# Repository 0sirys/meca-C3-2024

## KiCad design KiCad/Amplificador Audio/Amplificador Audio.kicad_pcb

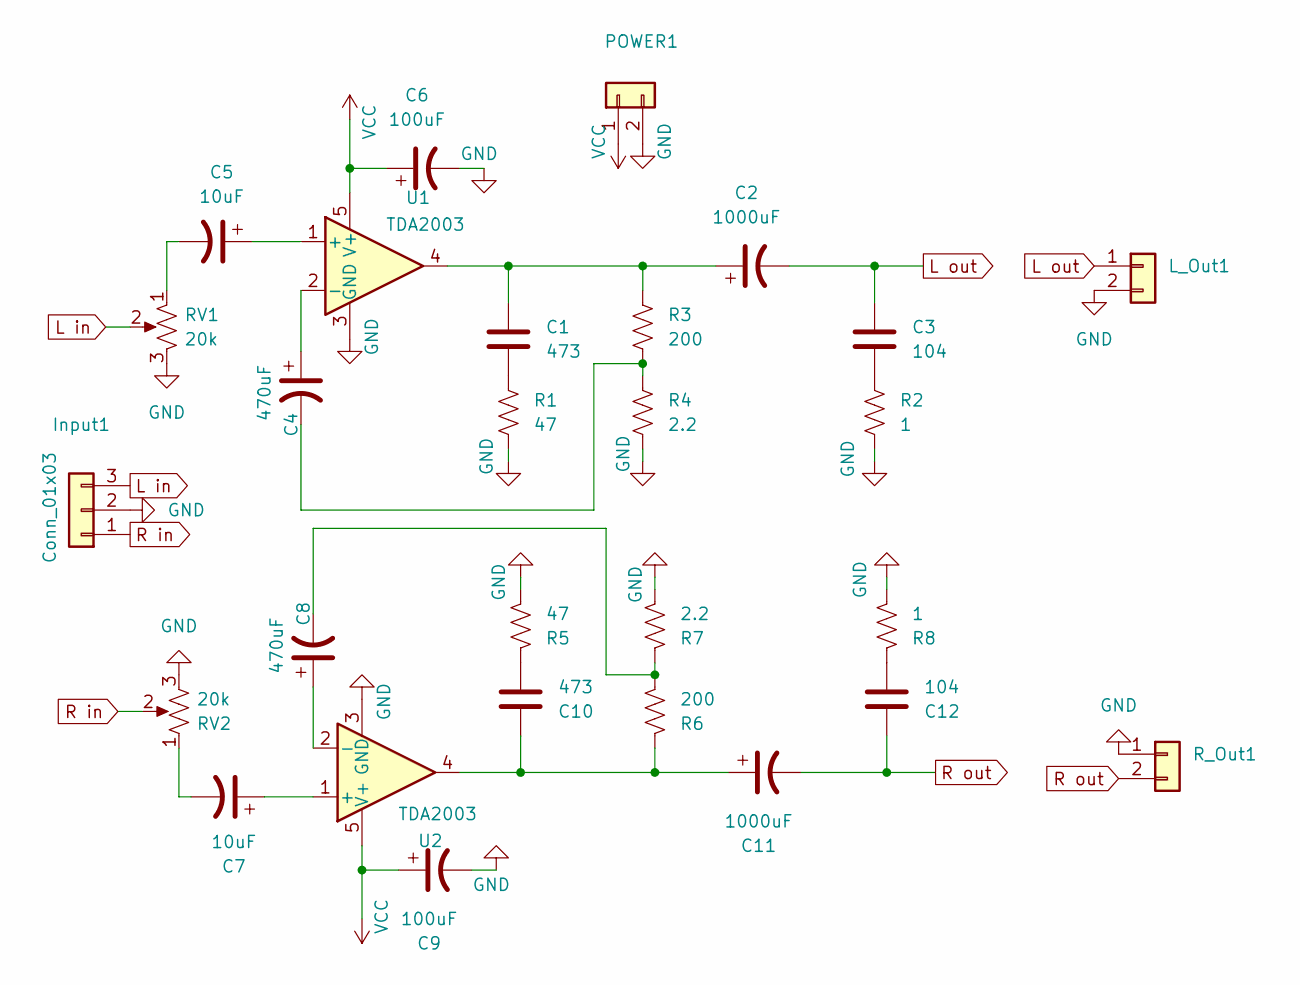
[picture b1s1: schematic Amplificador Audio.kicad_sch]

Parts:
C1, C10: 473; C_Disc_D3.0mm_W2.0mm_P2.50mm
C2, C11: 1000uF; CP_Radial_D16.0mm_P7.50mm
C3, C12: 104; C_Disc_D3.0mm_W2.0mm_P2.50mm
C4, C8: 470uF; CP_Radial_D10.0mm_P5.00mm
C5, C7: 10uF; CP_Radial_D5.0mm_P2.50mm
C6, C9: 100uF; CP_Radial_D10.0mm_P5.00mm
Input1: Conn_01x03; Molex_KK-254_AE-6410-03A_1x03_P2.54mm_Vertical
L_Out1: Conn_01x02; Molex_KK-254_AE-6410-02A_1x02_P2.54mm_Vertical
POWER1: CONN_01x02; Molex_KK-254_AE-6410-02A_1x02_P2.54mm_Vertical
R1, R5: 47; R_Axial_DIN0309_L9.0mm_D3.2mm_P15.24mm_Horizontal
R2, R8: 1; R_Axial_DIN0309_L9.0mm_D3.2mm_P15.24mm_Horizontal
R3, R6: 200; R_Axial_DIN0309_L9.0mm_D3.2mm_P15.24mm_Horizontal
R4, R7: 2.2; R_Axial_DIN0309_L9.0mm_D3.2mm_P15.24mm_Horizontal
RV1, RV2: 20k; Potentiometer_Runtron_RM-065_Vertical
R_Out1: Conn_01x02; Molex_KK-254_AE-6410-02A_1x02_P2.54mm_Vertical
U1, U2: TDA2003; TO-220-5_P3.4x3.7mm_StaggerOdd_Lead3.8mm_Vertical

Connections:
GND: C6.2, C9.2, Input1.2, L_Out1.2, POWER1.2, R1.2, R2.2, R4.2, R5.2, R7.2, R8.2, RV1.3, RV2.3, R_Out1.1, U1.3 (GND), U2.3 (GND)
L in: Input1.3, RV1.2
L out: C2.2, C3.1, L_Out1.1
unnamed: C1.1, C2.1, R3.1, U1.4
unnamed: C1.2, R1.1
unnamed: C3.2, R2.1
unnamed: C4.2, R3.2, R4.1
unnamed: C5.2, RV1.1
unnamed: C7.2, RV2.1
unnamed: C8.2, R6.2, R7.1
unnamed: C10.1, C11.1, R6.1, U2.4
unnamed: C10.2, R5.1
unnamed: C12.2, R8.1
unnamed: C5.1, U1.1 (+)
unnamed: C4.1, U1.2 (-)
unnamed: C7.1, U2.1 (+)
unnamed: C8.1, U2.2 (-)
R in: Input1.1, RV2.2
R out: C11.2, C12.1, R_Out1.2
VCC: C6.1, C9.1, POWER1.1, U1.5 (V+), U2.5 (V+)

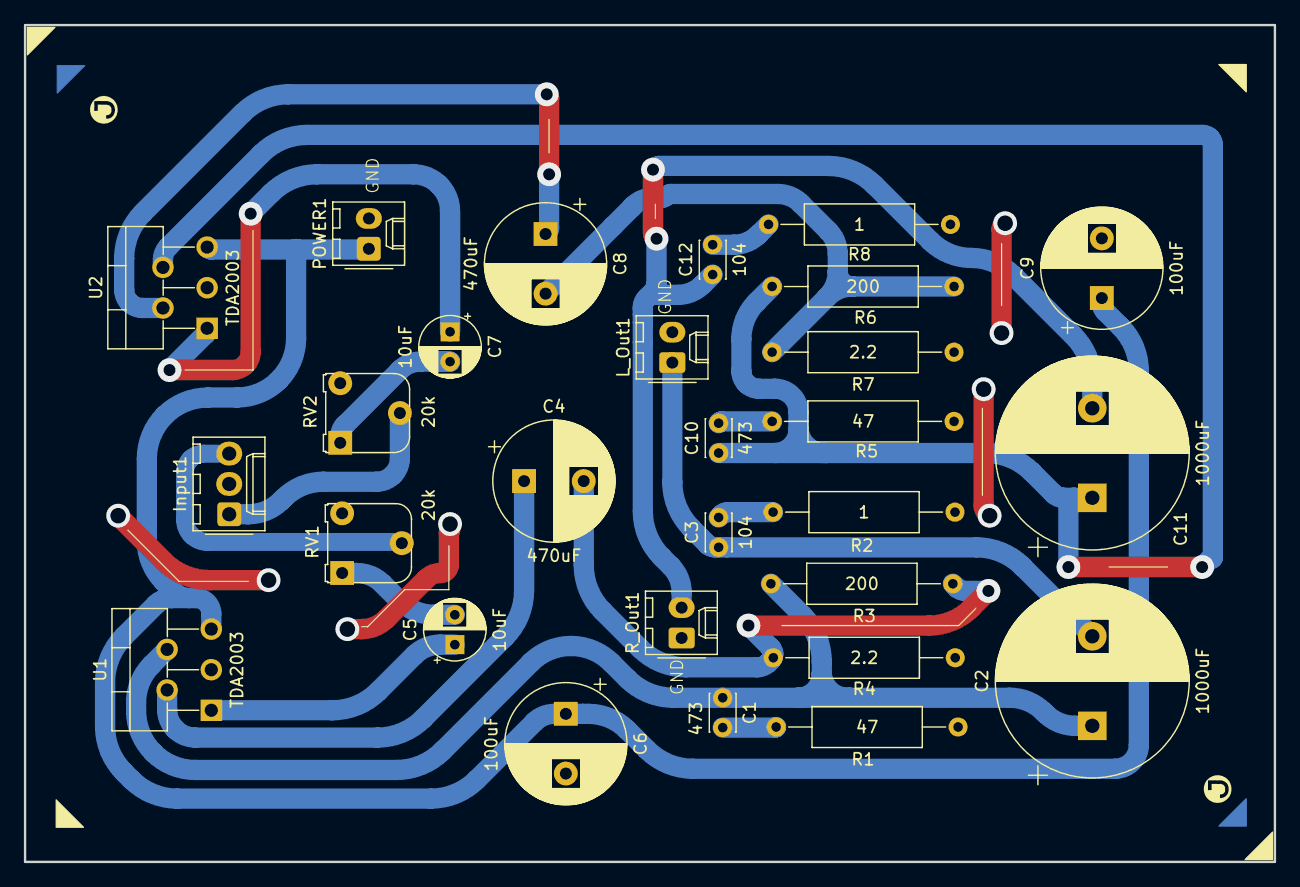
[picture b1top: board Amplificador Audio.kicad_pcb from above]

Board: 2 copper layers, 104.7 x 70.1 mm, 29 parts (0 on the bottom side), 20 nets.

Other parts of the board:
G2: LOGO; Logo

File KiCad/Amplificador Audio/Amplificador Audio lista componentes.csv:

Reference,Value,Qty
"C1,C10",473 mica,2
"C2,C11",1000uF,2
"C3,C12",104 mica,2
"C4,C8",470uF,2
"C5,C7",10uF,2
"C6,C9",100uF,2
Input1,Conn_01x03,1
"L_Out1,R_Out1",Conn_01x02,2
POWER1,Conn_01x02,1
"R1,R5",47,2
"R2,R8",1,2
"R3,R6",200,2
"R4,R7",2.2,2
"RV1,RV2",20k,2
"U1,U2",TDA2003,2

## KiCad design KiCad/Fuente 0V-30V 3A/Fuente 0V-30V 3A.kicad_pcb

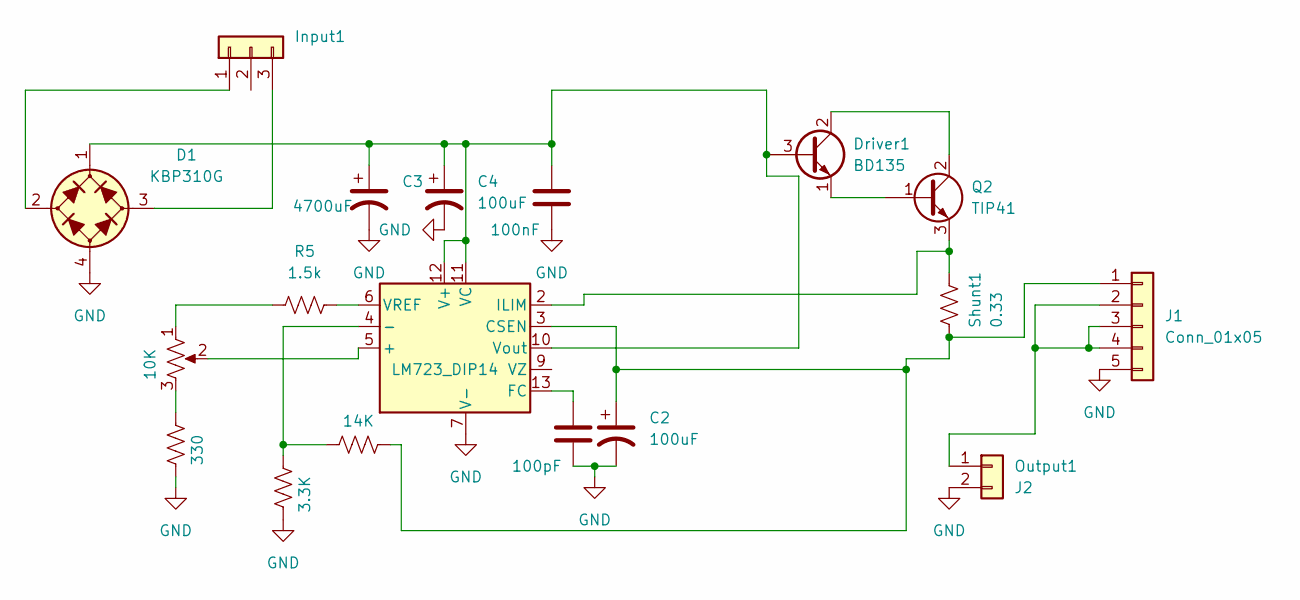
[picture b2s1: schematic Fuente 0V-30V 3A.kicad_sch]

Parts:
C1: 100pF; C_Disc_D5.0mm_W2.5mm_P2.50mm
C2, C4: 100uF; CP_Radial_Tantal_D8.0mm_P2.50mm
C3: 4700uF; C_Radial_D18.0mm_H35.5mm_P7.50mm
C5: 100nF; C_Disc_D5.0mm_W2.5mm_P2.50mm
D1: KBP310G; Diode_Bridge_KBP
Driver1: BD135; TO-126-3_Vertical
Input1: J3; Molex_KK-254_AE-6410-03A_1x03_P2.54mm_Vertical
J1: Conn_01x05; Molex_KK-254_AE-6410-05A_1x05_P2.54mm_Vertical
Output1: J2; Molex_KK-254_AE-6410-02A_1x02_P2.54mm_Vertical
Q2: TIP41; TO-220-3_Vertical
R1: 3.3K; R_Axial_DIN0411_L9.9mm_D3.6mm_P12.70mm_Horizontal
R4: 14K; R_Axial_DIN0411_L9.9mm_D3.6mm_P15.24mm_Horizontal
R5: 1.5k; R_Axial_DIN0411_L9.9mm_D3.6mm_P15.24mm_Horizontal
R6: 330; R_Axial_DIN0411_L9.9mm_D3.6mm_P15.24mm_Horizontal
RV1: 10K; Potentiometer_Alps_RK163_Single_Horizontal
Shunt1: 0.33; R_Axial_Power_L20.0mm_W6.4mm_P25.40mm
U1: LM723_DIP14; DIP-14_W7.62mm

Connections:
GND: C1.1, C2.2, C3.2, C4.2, C5.1, D1.4 (-), J1.5, Output1.2, R1.2, R6.1, U1.7 (V-)
unnamed: D1.2 (1), Input1.1
unnamed: D1.3 (2), Input1.3
unnamed: C3.1, C4.1, C5.2, D1.1 (+), Driver1.3 (B), U1.10 (Vout), U1.11 (VC), U1.12 (V+)
unnamed: Driver1.2 (C), Q2.2 (C)
unnamed: Driver1.1 (E), Q2.1 (B)
unnamed: C2.1, J1.1, R4.2, Shunt1.2, U1.3 (CSEN)
unnamed: J1.2, J1.3, J1.4, Output1.1
unnamed: Q2.3 (E), Shunt1.1, U1.2 (ILIM)
unnamed: R5.1, RV1.1
unnamed: R6.2, RV1.3
unnamed: RV1.2, U1.5 (+)
unnamed: R1.1, R4.1, U1.4 (-)
unnamed: C1.2, U1.13 (FC)
unnamed: R5.2, U1.6 (VREF)

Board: 2 copper layers, 18 parts (0 on the bottom side), 15 nets, no tracks yet.

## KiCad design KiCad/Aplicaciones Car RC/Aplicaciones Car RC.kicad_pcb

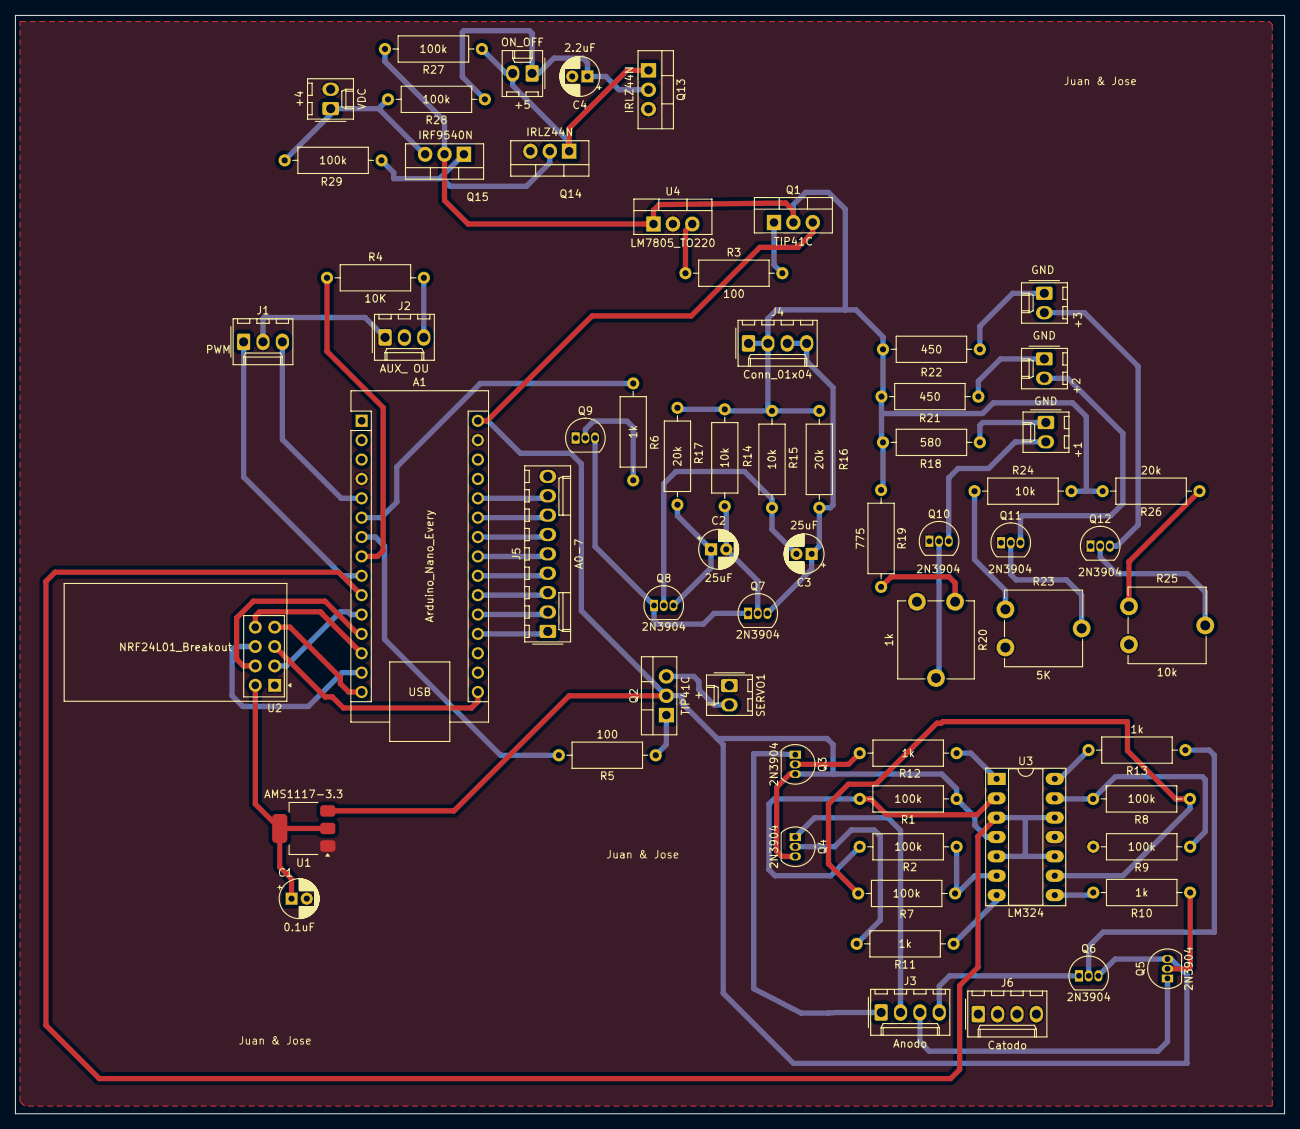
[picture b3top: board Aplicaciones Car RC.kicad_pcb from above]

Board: 2 copper layers, 166.4 x 144.0 mm, 65 parts (0 on the bottom side), 67 nets.

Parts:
+1, +2, +3: GND; Molex_KK-254_AE-6410-02A_1x02_P2.54mm_Vertical
+4: VDC; Molex_KK-254_AE-6410-02A_1x02_P2.54mm_Vertical
+5: ON_OFF; Molex_KK-254_AE-6410-02A_1x02_P2.54mm_Vertical
A1: Arduino_Nano_Every; Arduino_Nano
C1: 0.1uF; CP_Radial_D5.0mm_P2.00mm
C2, C3: 25uF; CP_Radial_D5.0mm_P2.00mm
C4: 2.2uF; CP_Radial_D5.0mm_P2.00mm
J1: PWM; Molex_KK-254_AE-6410-03A_1x03_P2.54mm_Vertical
J2: AUX_ OU; Molex_KK-254_AE-6410-03A_1x03_P2.54mm_Vertical
J3: Anodo; Molex_KK-254_AE-6410-04A_1x04_P2.54mm_Vertical
J4: Conn_01x04; Molex_KK-254_AE-6410-04A_1x04_P2.54mm_Vertical
J5: A0-7; Molex_KK-254_AE-6410-09A_1x09_P2.54mm_Vertical
J6: Catodo; Molex_KK-254_AE-6410-04A_1x04_P2.54mm_Vertical
Q1, Q2: TIP41C; TO-220-3_Vertical
Q3, Q4, Q5, Q6, Q7, Q8, Q9, Q10, Q11, Q12: 2N3904; TO-92_Inline
Q13, Q14: IRLZ44N; TO-220-3_Vertical
Q15: IRF9540N; TO-220-3_Vertical
R1, R2, R7, R8, R9, R27, R28, R29: 100k; R_Axial_DIN0309_L9.0mm_D3.2mm_P12.70mm_Horizontal
R3, R5: 100; R_Axial_DIN0309_L9.0mm_D3.2mm_P12.70mm_Horizontal
R4: 10K; R_Axial_DIN0309_L9.0mm_D3.2mm_P12.70mm_Horizontal
R6, R10, R11, R12, R13: 1k; R_Axial_DIN0309_L9.0mm_D3.2mm_P12.70mm_Horizontal
R14, R15, R24: 10k; R_Axial_DIN0309_L9.0mm_D3.2mm_P12.70mm_Horizontal
R16, R17, R26: 20k; R_Axial_DIN0309_L9.0mm_D3.2mm_P12.70mm_Horizontal
R18: 580; R_Axial_DIN0309_L9.0mm_D3.2mm_P12.70mm_Horizontal
R19: 775; R_Axial_DIN0309_L9.0mm_D3.2mm_P12.70mm_Horizontal
R20: 1k; Potentiometer_ACP_CA9-V10_Vertical
R21, R22: 450; R_Axial_DIN0309_L9.0mm_D3.2mm_P12.70mm_Horizontal
R23: 5K; Potentiometer_ACP_CA9-V10_Vertical
R25: 10k; Potentiometer_ACP_CA9-V10_Vertical
SERVO1: +; Molex_KK-254_AE-6410-02A_1x02_P2.54mm_Vertical
U1: AMS1117-3.3; SOT-223-3_TabPin2
U2: NRF24L01_Breakout; nRF24L01_Breakout
U3: LM324; DIP-14_W7.62mm_Socket_LongPads
U4: LM7805_TO220; TO-220-3_Vertical

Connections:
3.3: C1.1, U1.2 (VO), U2.2 (VCC)
+5V: A1.30 (VIN), Q1.3 (E), Q2.2 (C), Q3.3 (C), Q4.3 (C), Q5.3 (C), Q6.3 (C), R1.1, U1.3 (VI), U3.4 (V+)
+14V: J4.1, J4.2, Q1.2 (C), Q15.2 (D), R14.2, R15.2, R16.2, R17.2, R18.1, R19.1, R21.1, R22.1, R24.2, R26.2, R27.2, U4.1 (VI)
CE: A1.11 (D8), U2.3 (CE)
CSN: A1.12 (D9), U2.4 (~CSN)
GND: +4.2, A1.4 (GND), A1.29 (GND), C1.2, C4.2, J1.2, J2.1, J5.9, J6.1, J6.2, J6.3, J6.4, Q9.1 (E), Q10.1 (E), Q11.1 (E), Q12.1 (E), Q13.3 (S), Q14.3 (S), R9.2, R20.1 (a), R23.1 (a), R25.1 (a), SERVO1.1, U1.1 (GND), U2.1 (GND), U3.11 (V-), U4.2 (GND)
IRQ: A1.13 (D10), U2.8 (IRQ)
ITON: A1.8 (D5), R4.1
Luces: A1.6 (D3), R6.1
MISO: A1.15 (MISO), U2.7 (MISO)
MOSI: A1.14 (MOSI), U2.6 (MOSI)
unnamed: +1.1, R18.2
unnamed: +1.2, Q10.3 (C)
unnamed: +2.1, R21.2
unnamed: +2.2, Q11.3 (C)
unnamed: +3.1, R22.2
unnamed: +3.2, Q12.3 (C)
unnamed: +4.1, Q15.3 (S), R28.2, R29.2
unnamed: +5.1, C4.1, Q13.2 (D), R28.1
unnamed: +5.2, Q13.1 (G), Q14.1 (G), R27.1
unnamed: A1.19 (A0), J5.1
unnamed: A1.20 (A1), J5.2
unnamed: A1.21 (A2), J5.3
unnamed: A1.22 (A3), J5.4
unnamed: A1.25 (A6), J5.7
unnamed: A1.26 (A7), J5.8
unnamed: A1.24 (SCL/A5), J5.6
unnamed: A1.23 (SDA/A4), J5.5
unnamed: J2.3, R4.2
unnamed: J3.1, Q3.1 (E)
unnamed: J3.2, Q4.1 (E)
unnamed: J3.3, Q5.1 (E)
unnamed: J3.4, Q6.1 (E)
unnamed: C3.1, J4.3, J4.4, Q7.3 (C), R16.1
unnamed: Q1.1 (B), R3.2
unnamed: Q2.1 (B), R5.1
unnamed: Q2.3 (E), SERVO1.2
unnamed: Q3.2 (B), R12.1
unnamed: Q4.2 (B), R11.2
unnamed: Q5.2 (B), R10.1
unnamed: Q6.2 (B), R13.1
unnamed: C2.2, Q7.2 (B), R14.1
unnamed: Q7.1 (E), Q8.1 (E), Q9.3 (C)
unnamed: C3.2, Q8.2 (B), R15.1
unnamed: C2.1, Q8.3 (C), R17.1
unnamed: Q9.2 (B), R6.2
unnamed: Q10.2 (B), R20.2 (b)
unnamed: Q11.2 (B), R23.2 (b)
unnamed: Q12.2 (B), R25.2 (b)
unnamed: Q14.2 (D), Q15.1 (G), R29.1
unnamed: R10.2, U3.8
unnamed: R11.1, U3.7
unnamed: R12.2, U3.1
unnamed: R13.2, U3.14
unnamed: R19.2, R20.3 (c)
unnamed: R23.3 (c), R24.1
unnamed: R25.3 (c), R26.1
unnamed: R1.2, R2.1, U3.2 (-)
unnamed: R2.2, R7.1, U3.6 (-)
unnamed: R7.2, R8.1, U3.9 (-)
unnamed: R8.2, R9.1, U3.13 (-)
unnamed: R3.1, U4.3 (VO)
PWM D: A1.7 (D4), R5.2
PWM M: A1.5 (D2), J1.3
PWM M2: A1.9 (D6), J1.1
PWM S: A1.10 (D7), U3.3 (+), U3.5 (+), U3.10 (+), U3.12 (+)
SCK: A1.16 (SCK), U2.5 (SCK)

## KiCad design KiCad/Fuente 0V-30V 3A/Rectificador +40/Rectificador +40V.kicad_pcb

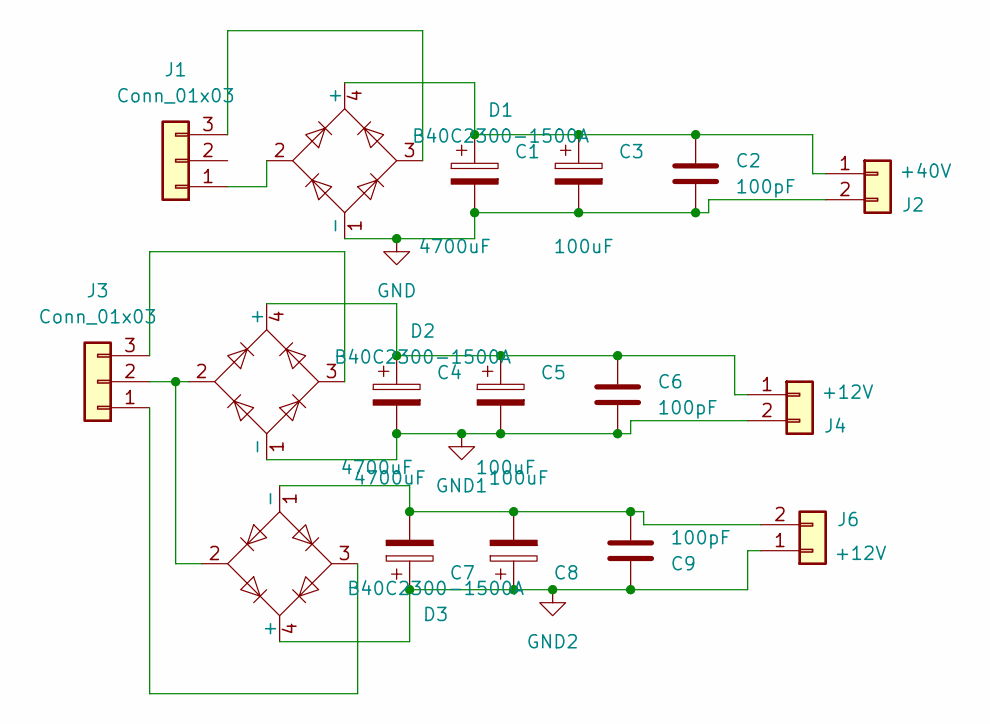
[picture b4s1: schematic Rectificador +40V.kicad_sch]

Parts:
C1, C4, C7: 4700uF; C_Radial_D18.0mm_H35.5mm_P7.50mm
C2, C6, C9: 100pF; C_Disc_D3.4mm_W2.1mm_P2.50mm
C3, C5, C8: 100uF; C_Radial_D10.0mm_H16.0mm_P5.00mm
D1, D2, D3: B40C2300-1500A; Diode_Bridge_19.0x3.5x10.0mm_P5.0mm
J1, J3: Conn_01x03; Molex_KK-254_AE-6410-03A_1x03_P2.54mm_Vertical
J2: +40V; Molex_KK-254_AE-6410-02A_1x02_P2.54mm_Vertical
J4, J6: +12V; Molex_KK-254_AE-6410-02A_1x02_P2.54mm_Vertical

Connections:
unnamed: C1.1, C2.1, C3.1, D1.4 (+), J2.1
unnamed: C1.2, C2.2, C3.2, D1.1 (-), J2.2
unnamed: C4.1, C5.1, C6.1, D2.4 (+), J4.1
unnamed: C4.2, C5.2, C6.2, D2.1 (-), J4.2
unnamed: C7.1, C8.1, C9.1, D3.4 (+), J6.1
unnamed: C7.2, C8.2, C9.2, D3.1 (-), J6.2
unnamed: D1.2, J1.1
unnamed: D1.3, J1.3
unnamed: D3.3, J3.1
unnamed: D2.2, D3.2, J3.2
unnamed: D2.3, J3.3

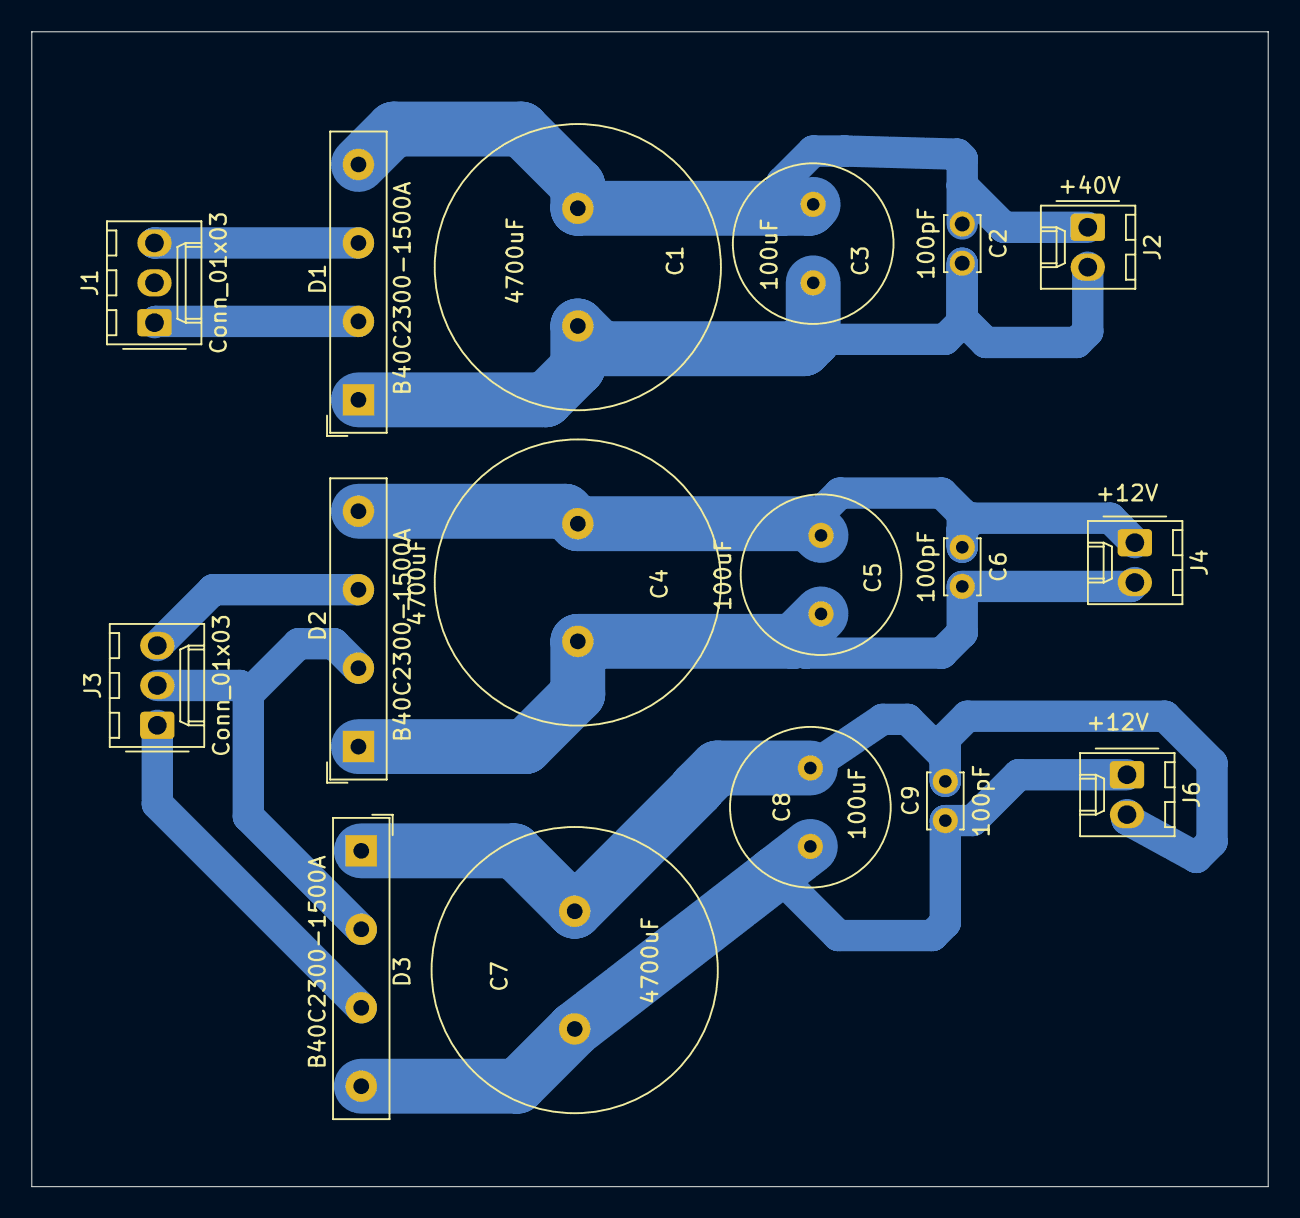
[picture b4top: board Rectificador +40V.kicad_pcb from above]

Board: 2 copper layers, 78.8 x 73.6 mm, 17 parts (0 on the bottom side), 11 nets.

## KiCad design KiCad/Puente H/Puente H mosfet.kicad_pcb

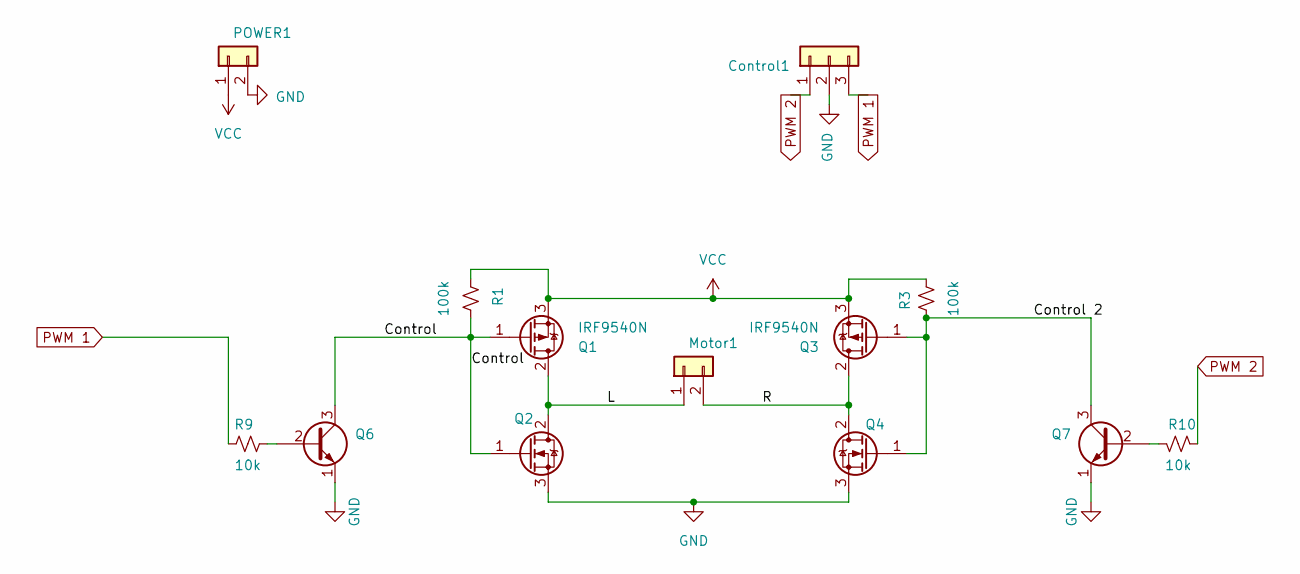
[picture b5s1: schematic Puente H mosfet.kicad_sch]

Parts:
Control1: Conn_01x03; Molex_KK-254_AE-6410-03A_1x03_P2.54mm_Vertical
Motor1: Conn_01x02; TerminalBlock_bornier-2_P5.08mm
POWER1: Conn_01x02; TerminalBlock_bornier-2_P5.08mm
Q1, Q3: IRF9540N; TO-220F-3_Vertical
Q2, Q4: IRF540N; TO-220F-3_Vertical
Q6, Q7: 2N3904; TO-92_Inline_Wide
R1, R3: 100k; R_Axial_DIN0207_L6.3mm_D2.5mm_P10.16mm_Horizontal
R9, R10: 10k; R_Axial_DIN0207_L6.3mm_D2.5mm_P10.16mm_Horizontal

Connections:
/Control: Q1.1 (G), Q2.1 (G), Q6.3 (C), R1.2
/Control 2: Q3.1 (G), Q4.1 (G), Q7.3 (C), R3.1
/L: Motor1.1, Q1.2 (D), Q2.2 (D)
/R: Motor1.2, Q3.2 (D), Q4.2 (D)
GND: Control1.2, POWER1.2, Q2.3 (S), Q4.3 (S), Q6.1 (E), Q7.1 (E)
unnamed: Q6.2 (B), R9.2
unnamed: Q7.2 (B), R10.2
PWM 1: Control1.3, R9.1
PWM 2: Control1.1, R10.1
VCC: POWER1.1, Q1.3 (S), Q3.3 (S), R1.1, R3.2

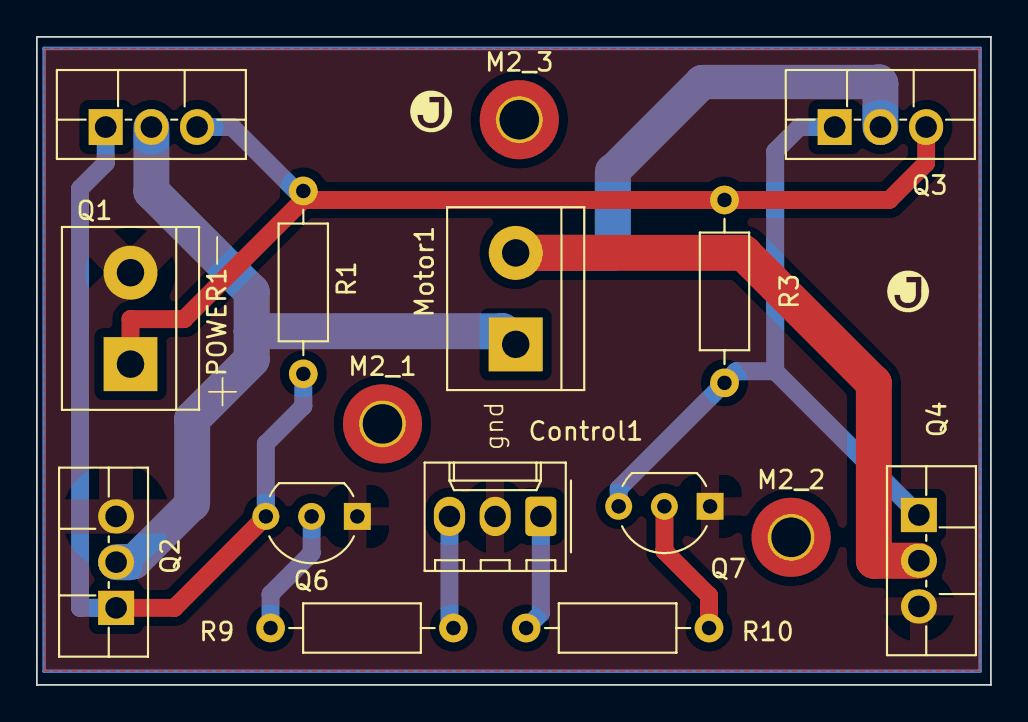
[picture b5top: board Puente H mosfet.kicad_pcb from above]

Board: 2 copper layers, 53.0 x 36.0 mm, 17 parts (0 on the bottom side), 10 nets.

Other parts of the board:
G2: LOGO; Logo
M2_1, M2_2, M2_3: MountingHole_2.2mm_M2_Pad_TopBottom

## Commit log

2024-09-11 Ajuste
2024-09-13 Controles Automaticos added
2024-09-16 Avance Cuestionario 1
2024-09-16 Backup c2 electronica 2
2024-09-16 Cuestionario 1 Done, Marcha/paro Done
2024-09-16 Nivel de agua
2024-09-17 kicad projects added
2024-09-17 Transistor como Switch Done
2024-09-17 Fix nivel de agua
2024-09-18 Export Kicad projects to other repository
2024-09-18 Practica 1 BTJ LAB
2024-09-21 Practica BJT pdf done
2024-09-23 stash
2024-09-23 Backup Kicad 3_party plugins
2024-09-25 BJT seguidor ongoing
2024-09-25 BJT seguidor ongoing 1.0
2024-10-04 Proceso de manofactura Added
2024-10-11 Controles cuestionario start
2024-10-11 Resources updated
2024-10-14 Cuestionario ongoing
2024-10-14 Cuestionario proceso de manofactura 1-5 done
2024-10-15 Practica Teoria Mosfet ongoing
2024-10-16 Practica Lab FET ongoing
2024-10-17 Practica Fet done
2024-10-18 Cuestionario ongoin 0.1
2024-10-18 Cuestionario 0.2
2024-10-23 Multisim Circuit
2024-10-28 Lab Opamp done
2024-11-07 Abanico ongoing
2024-11-11 Nuevos
2024-11-20 Codigo
2024-11-20 fix code
2024-12-01 pc micelanea
2024-12-02 Cuestionario
2024-12-02 Hot fix Toggle_Buttons
2025-01-27 Adios
2025-01-27 Wipe
2025-01-27 Practica 1 CNC Done
2025-01-28 Practica 2 Lab digital DONE
2025-02-03 Practica 3 Lab Ongoing
2025-02-03 Lab electronica industrial done
2025-02-04 lab electronica digital ongoin
2025-02-04 Practica 3 lab Done
2025-02-04 verilog hot-fix output
2025-02-04 verilog hot-fix
2025-02-06 APA 7ma edicion Template
2025-02-06 APA 7ma edicion Template hot fix done
